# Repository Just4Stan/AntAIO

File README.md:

# AntAIO

Open-source **antweight / beetleweight combat-robot all-in-one** controller — an
ExpressLRS receiver, a 6-axis IMU, and a **triple brushed-DC ESC** on one tiny
board, in the spirit of the [Malenki Nano](https://turnabot.com/products/malenki-nano-integrated-6-channel-triple-electronic-speed-controller-receiver-combo). Built on
the **OpenRX-Lite** ELRS core (ESP32-C3 + SX1281, 2.4 GHz) and forked from
[`incutec-hw/OpenRX`](https://github.com/incutec-hw/OpenRX).

> [!WARNING]
> **Prototype — not validated, not fab-ready.** This board has open
> safety-critical issues (uncommanded drive-motor motion at power-up, and the
> programming interface shares pins with the motor outputs). It drives combat-robot
> motors **including a weapon** — do not build or power it without reading the
> review first. See **[hardware/REVIEW.md](hardware/REVIEW.md)** (full design
> review) and **[CHANGELIST.md](CHANGELIST.md)** (verified to-do list).

## What it is

A single **10.00 × 21.50 mm**, 6-layer board that replaces the usual *RX + 2 drive ESCs +
weapon ESC + gyro* stack of an antweight robot with one MCU-driven combo:

- **Radio link** — ExpressLRS 2.4 GHz (Semtech SX1281) for RC control + telemetry,
  plus the ESP32-C3's own Wi-Fi for OTA config.
- **Motion sensing** — LSM6DS3TR-C 6-axis IMU (gyro + accel) for heading-hold /
  self-right / melty-style control in firmware.
- **Three brushed-DC motor channels** — two drive + one weapon, each a TI DRV8212
  H-bridge fed directly from the battery.
- **Single-cell-friendly power** — buck-boost holds a 5 V rail as the pack sags
  under weapon load, with a linear 3.3 V logic rail and reverse-polarity protection.

Everything is controlled by the **ESP32-C3**: RC decode, mixing, gyro stabilization,
and the three motor PWM outputs all run on-chip.

## Architecture

```
            +BATT (1–2S LiPo)
              │
        Q2  AON7407  ── reverse-polarity P-FET
              ├─────────────► VM ─► DRV8212 ×3 ─► LEFT / RIGHT drive + WEAPON motors
              │
        U8  TPS63070 buck-boost ─► +5V ─► U4 TLV75533 LDO ─► +3V3 (logic)
                                                              │
   ┌──────────────────────────────────────────────────────────┤
   │                                                            │
 U1 ESP32-C3 ──SPI──► U3 SX1281 (2.4 GHz ELRS) ─► FL1 BPF ─► link antenna
   │            └────► U2 LSM6DS3TR-C IMU                 ESP Wi-Fi ─► AE1
   ├── 3× PWM ─► DRV8212 IN/EN  (U6 LEFT, U10 RIGHT, U11 WEAPON)
   ├── ADC ──── VSENSE (battery voltage divider)
   └── GPIO ──► WS2812B status LED (D1)
```

## Specifications

| Block | Part | Notes |
|---|---|---|
| **MCU** | Espressif **ESP32-C3FH4** (U1, QFN-32) | RISC-V, 4 MB embedded flash, 2.4 GHz Wi-Fi |
| **Link radio** | Semtech **SX1281** (U3) | 2.4 GHz, internal DC-DC, 52 MHz TCXO (OSC1), BPF FL1 (2450FM07D0034T) → link antenna |
| **IMU** | **LSM6DS3TR-C** (U2) | 6-axis accel+gyro, 4-wire SPI on the shared radio bus, dedicated CS |
| **Motor drivers** | 3× TI **DRV8212DSGR** | U6 = LEFT drive, U10 = RIGHT drive, U11 = WEAPON; PH/EN mode; VM = +BATT |
| **Buck-boost** | TI **TPS63070** (U8) | +BATT → 5 V; holds the rail across the 1S–2S sag range |
| **LDO** | **TLV75533PDQNR** (U4) | 5 V → 3.3 V logic rail |
| **Reverse protection** | **AON7407** P-FET (Q2) | on +BATT |
| **Status LED** | WS2812B (D1) | addressable RGB |
| **Battery** | **1–2S LiPo (≤ 8.4 V)** | DRV8212 VM is 12 V abs-max — **2S is the hard ceiling; 3S destroys the drivers** |
| **Board** | 10.00 × 21.50 mm, 6-layer | components both sides |

## I/O pads

Solder pads carry the external interface (silk in parentheses):

| Pad | Net | Function |
|---|---|---|
| `+` / `–` | `+BATT` / `GND` | Battery in (1–2S) |
| `5U` | `+5V` | 5 V buck-boost output (servo / accessory) |
| `GND` | `GND` | Ground |
| `S` | GPIO | Signal / spare control pad |
| `BOOT` | GPIO 9 | Hold low at power-up for UART download mode |
| `R` / `T` | UART0 RX / TX | Flashing & serial console (also the right-drive lines — flash with motor battery OFF) |

Motor outputs (OUT1/OUT2 of each DRV8212) and the weapon channel land on the large
copper pads along the board edge.

## ESP32-C3 pin map (as currently drawn)

| GPIO | Pin | Function | GPIO | Pin | Function |
|---|---|---|---|---|---|
| 0 | 4 | VSENSE (battery ADC) | 8 | 14 | WS2812 LED *(strap)* |
| 1 | 5 | Radio DIO1 | 9 | 15 | BOOT *(strap)* |
| 2 | 6 | IMU CS *(strap)* | 10 | 16 | WEAPON_EN |
| 3 | 8 | Radio BUSY | 18 | 25 | LEFT_PH *(USB D−)* |
| 4 | 9 | SPI MOSI | 19 | 26 | LEFT_EN *(USB D+)* |
| 5 | 10 | SPI MISO | U0RXD | 27 | RIGHT_PH |
| 6 | 12 | SPI SCK | U0TXD | 28 | RIGHT_EN |
| 7 | 13 | Radio NSS | GND/EP | 33 | GND |

> [!IMPORTANT]
> The drive-motor enables currently sit on the USB (GPIO18/19) and UART0
> (U0RXD/U0TXD) pins, which are driven **high at reset** — enabling both drive
> motors before firmware runs. The planned fix re-maps PH↔EN onto reset-quiet pins
> and gates the H-bridges behind a default-off arm switch. **Do not treat this pin
> map as final** — track it in [CHANGELIST.md](CHANGELIST.md).

## Flashing

- **UART:** hold `BOOT` low, power-cycle, flash over the `R`/`T` (U0RXD/U0TXD) pads
  **with the motor battery disconnected** (these pins also drive the right motor).
- **Wi-Fi OTA:** ExpressLRS SoftAP, after an initial wired flash.

The ELRS link runs upstream **ExpressLRS** (`Unified_ESP32C3_2400_RX`, ≥ 3.5.0).
The combat-robot mixing, IMU stabilization, and motor-PWM control are application
firmware layered on top (separate; not in this hardware repo).

## Repository

AntAIO began as a fork of [`incutec-hw/OpenRX`](https://github.com/incutec-hw/OpenRX)
— the **OpenRX-Lite** ELRS core (ESP32-C3 + SX1281) extended into a combat-robot
all-in-one. The other OpenRX receiver variants are not part of this repo.

```
AntAIO/
├── hardware/             AntAIO board: ELRS RX + IMU + triple brushed ESC
│   ├── AntAIO.kicad_{pro,sch,pcb}
│   ├── esp32c3_sx1281_lite.kicad_sch   ELRS core sub-sheet
│   ├── REVIEW.md         full design review (pin/datasheet/electrical)
│   └── DESIGN.md
├── shared/libs/          project-local KiCad symbols / footprints / 3D models
├── shared/elrs-targets/  ExpressLRS hardware-target JSON
├── datasheets/common/    local datasheet cache
├── images/               board renders
└── CHANGELIST.md         verified open / done items
```

KiCad 9/10; **project-local libraries only** (no global dependencies). Board renders
are produced with the shared `render_board.py` tool (vias + solder paste stripped,
transparent square).

## License

Hardware: **CERN Open Hardware Licence Version 2 — Strongly Reciprocal**
([CERN-OHL-S-2.0](https://ohwr.org/cern_ohl_s_v2.txt)). See [LICENSE](LICENSE).
Firmware: MIT.

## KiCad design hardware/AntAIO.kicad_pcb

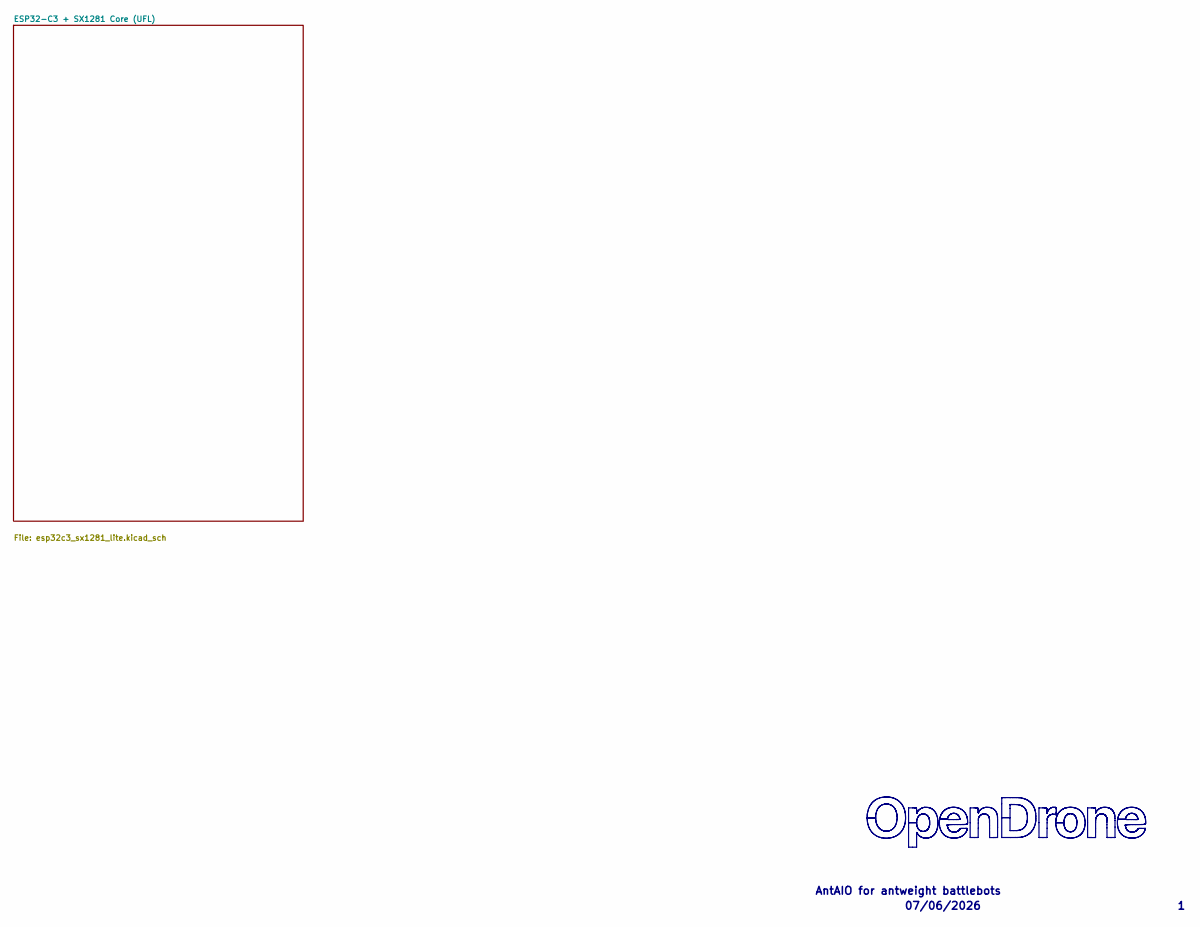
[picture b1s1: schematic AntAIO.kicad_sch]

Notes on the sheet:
07/06/2026
AntAIO for antweight battlebots

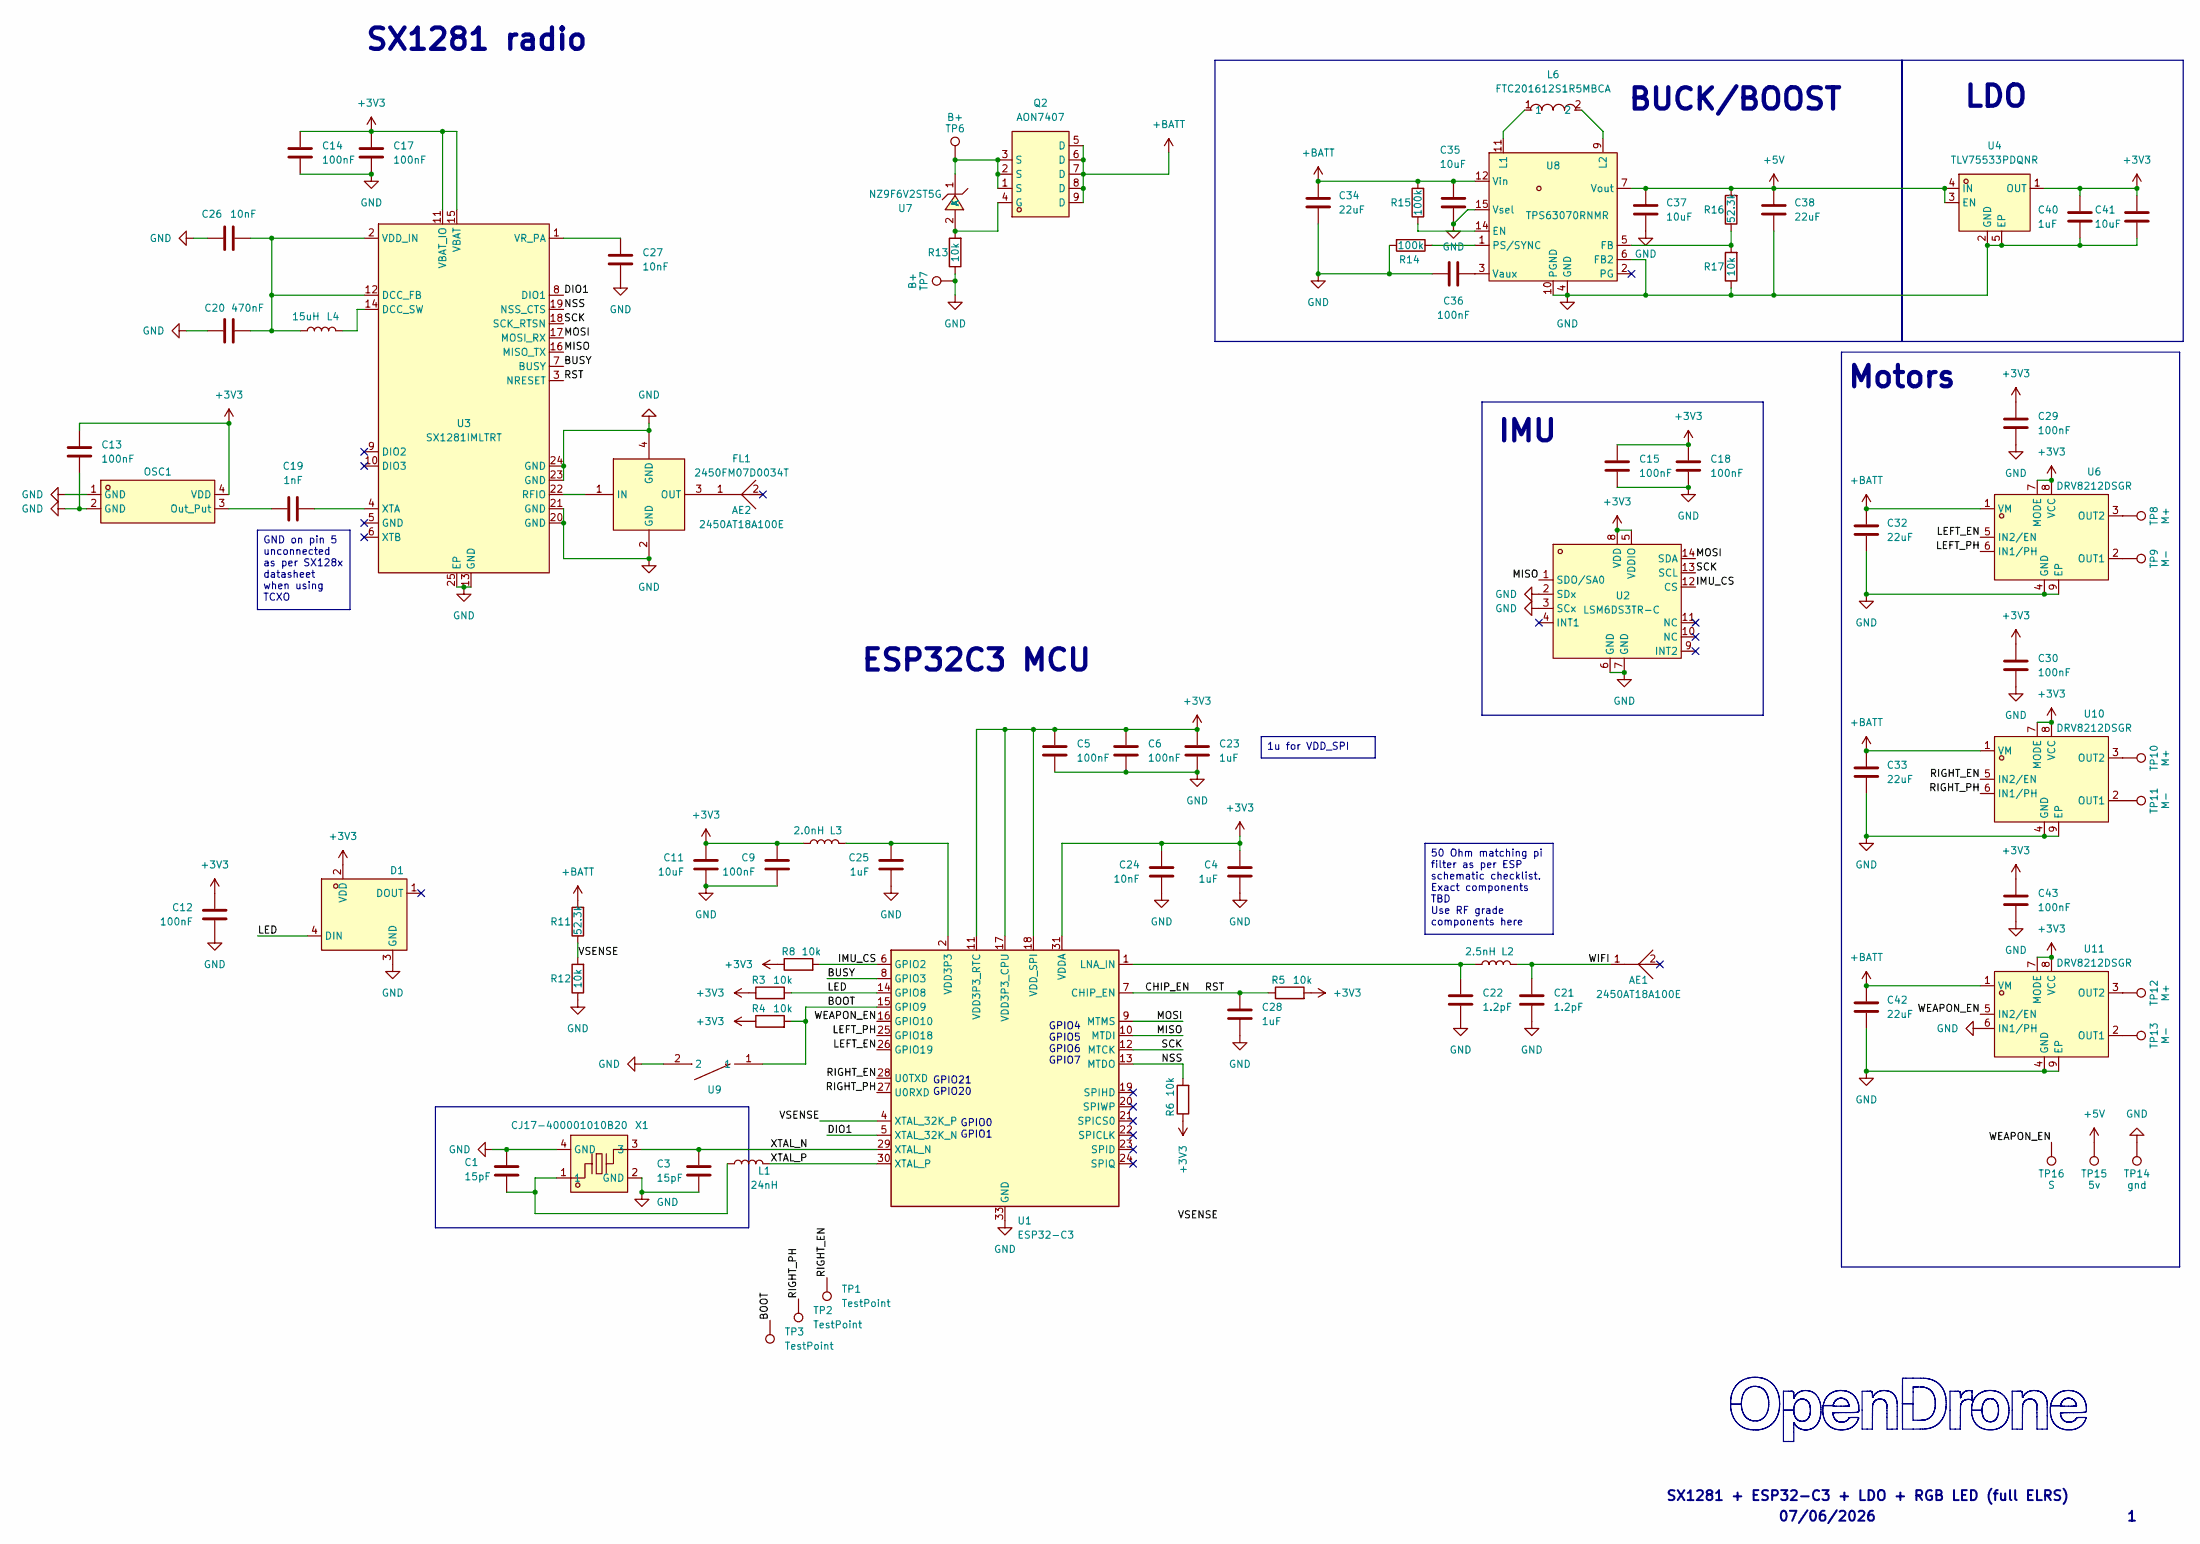
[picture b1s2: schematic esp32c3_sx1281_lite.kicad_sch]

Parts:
AE1, AE2: 2450AT18A100E; ANT-SMD_L3.2-W1.6; LCSC Part C89334
C1, C3: 15pF; C_0201_0603Metric; LCSC C85891
C4, C23, C25, C28, C40: 1uF; C_0201_0603Metric; LCSC C76935
C5, C6, C9, C12, C13, C14, C15, C17, C18, C29, C30, C36, C43: 100nF; C_0201_0603Metric; LCSC C76939
C11: 10uF; C_0402_1005Metric; LCSC C76991
C19: 1nF; C_0201_0603Metric; LCSC C66942
C20: 470nF; C_0201_0603Metric; LCSC C85926
C21, C22: 1.2pF; C_0201_0603Metric; LCSC C85895
C24, C26, C27: 10nF; C_0201_0603Metric; LCSC C2168164
C32, C33, C34, C38, C42: 22uF; C_0805_2012Metric; LCSC C45783
C35, C37: 10uF; C_0603_1608Metric; LCSC C92487
C41: 10uF; C_0402_1005Metric; LCSC C15525
D1: XL-1010RGBC-WS2812B; LED-SMD_4P-L1.0-W1.0-TL_XL-1010RGBC-WS2812B; LCSC Part C5349953
FL1: 2450FM07D0034T; FILTER-SMD_4P-L1.0-W0.5-L; MPN 2450FM07D0034T; LCSC Part C2651081
L1: 24nH; L_0201_0603Metric; LCSC C206441
L2: 2.5nH; L_0201_0603Metric; LCSC C206435
L3: 2.0nH; L_0201_0603Metric; LCSC C86125
L4: 15uH; L_0805_2012Metric
L6: FTC201612S1R5MBCA; IND-SMD_L2.0-W1.6; MPN FTC201612S1R5MBCA; LCSC Part C5832350
OSC1: OW7EL89CENUNFAYLC-52M; OSC-SMD_4P-L2.0-W1.6-BL_TXC_7Z; LCSC Part C22434896
Q2: AON7407; DFN-8_L3.0-W3.0-P0.65-BL; MPN AON7407; LCSC Part C176756
R3, R4, R5, R6, R8, R12, R13, R17: 10k; R_0201_0603Metric; LCSC C106225
R11, R16: 52.3k; R_0201_0603Metric; LCSC C2575555
R14, R15: 100k; R_0201_0603Metric; LCSC C106224
TP1, TP2, TP3: TestPoint; TestPoint_Pad_D1.0mm
TP6, TP7: B+; SolderPad_1.2x2.0mm
TP8, TP10, TP12: M+; SolderPad_1.2x2.0mm
TP9, TP11, TP13: M-; SolderPad_1.2x2.0mm
TP14: gnd; SolderPad_1.2x2.0mm
TP15: 5v; SolderPad_1.2x2.0mm
TP16: S; SolderPad_1.2x2.0mm
U1: ESP32-C3; QFN-32-1EP_5x5mm_P0.5mm_EP3.7x3.7mm
U2: LSM6DS3TR-C; LGA-14_3x2.5mm_P0.5mm_LayoutBorder3x4y; MPN LSM6DS3TR-C; LCSC Part C967633
U3: SX1281IMLTRT; QFN-24_L4.0-W4.0-P0.50-TL-EP2.6; LCSC Part C2151551
U4: TLV75533PDQNR; X2SON-4_L1.0-W1.0-P0.65-TL-EP; LCSC Part C2861882
U6, U10, U11: DRV8212DSGR; WSON-8_L2.0-W2.0-P0.50-TL-EP; MPN DRV8212DSGR; LCSC Part C2843766
U7: NZ9F6V2ST5G; SOD-923_L0.8-W0.6-LS1.0-RD; MPN NZ9F6V2ST5G; LCSC Part C896533
U8: TPS63070RNMR; VQFN-15_L3.0-W2.5-P0.50-BL; MPN TPS63070RNMR; LCSC Part C109322
U9: TS2306A 240GF MSM 9_C2976675; SW-SMD_4P-L3.0-W2.0-P0.85-LS3.5; LCSC Part C2976675
X1: CJ17-400001010B20; CRYSTAL-SMD_4P-L1.6-W1.2-BL; LCSC Part C2875272

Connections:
+3V3: C4.1, C5.1, C6.1, C9.1, C11.1, C12.1, C13.1, C14.1, C15.1, C17.1, C18.1, C23.1, C24.1, C29.1, C30.1, C40.1, C41.1, C43.1, D1.2 (VDD), L3.2, OSC1.4 (VDD), R3.1, R4.1, R5.2, R6.1, R8.1, U1.11 (VDD3P3_RTC), U1.17 (VDD3P3_CPU), U1.18 (VDD_SPI), U1.31 (VDDA), U1.32 (VDDA), U2.5 (VDDIO), U2.8 (VDD), U3.11 (VBAT_IO), U3.15 (VBAT), U4.1 (OUT), U6.7 (MODE), U6.8 (VCC), U10.7 (MODE), U10.8 (VCC), U11.7 (MODE), U11.8 (VCC)
+5V: C37.1, C38.1, R16.2, TP15.1 (1_1), U4.3 (EN), U4.4 (IN), U8.7 (Vout)
+BATT: C32.1, C33.1, C34.1, C35.1, C42.1, Q2.5 (D), Q2.6 (D), Q2.7 (D), Q2.8 (D), Q2.9 (D), R11.2, R15.2, U6.1 (VM), U8.12 (Vin), U10.1 (VM), U11.1 (VM)
/ESP32-C3 + SX1281 Core (UFL)/BOOT: R4.2, TP3.1 (1_1), U1.15 (GPIO9), U9.1
/ESP32-C3 + SX1281 Core (UFL)/BUSY: U1.8 (GPIO3), U3.7 (BUSY)
/ESP32-C3 + SX1281 Core (UFL)/CHIP_EN: C28.1, R5.1, U1.7 (CHIP_EN), U3.3 (NRESET)
/ESP32-C3 + SX1281 Core (UFL)/DIO1: U1.5 (XTAL_32K_N), U3.8 (DIO1)
/ESP32-C3 + SX1281 Core (UFL)/IMU_CS: R8.2, U1.6 (GPIO2), U2.12 (CS)
/ESP32-C3 + SX1281 Core (UFL)/LED: D1.4 (DIN), R3.2, U1.14 (GPIO8)
/ESP32-C3 + SX1281 Core (UFL)/LEFT_EN: U1.26 (GPIO19), U6.5 (IN2/EN)
/ESP32-C3 + SX1281 Core (UFL)/LEFT_PH: U1.25 (GPIO18), U6.6 (IN1/PH)
/ESP32-C3 + SX1281 Core (UFL)/MISO: U1.10 (MTDI), U2.1 (SDO/SA0), U3.16 (MISO_TX)
/ESP32-C3 + SX1281 Core (UFL)/MOSI: U1.9 (MTMS), U2.14 (SDA), U3.17 (MOSI_RX)
/ESP32-C3 + SX1281 Core (UFL)/NSS: R6.2, U1.13 (MTDO), U3.19 (NSS_CTS)
/ESP32-C3 + SX1281 Core (UFL)/RIGHT_EN: TP1.1 (1_1), U1.28 (U0TXD), U10.5 (IN2/EN)
/ESP32-C3 + SX1281 Core (UFL)/RIGHT_PH: TP2.1 (1_1), U1.27 (U0RXD), U10.6 (IN1/PH)
/ESP32-C3 + SX1281 Core (UFL)/SCK: U1.12 (MTCK), U2.13 (SCL), U3.18 (SCK_RTSN)
/ESP32-C3 + SX1281 Core (UFL)/VSENSE: R11.1, R12.2, U1.4 (XTAL_32K_P)
/ESP32-C3 + SX1281 Core (UFL)/WEAPON_EN: TP16.1 (1_1), U1.16 (GPIO10), U11.5 (IN2/EN)
/ESP32-C3 + SX1281 Core (UFL)/WIFI: AE1.1, C21.1, L2.1
/ESP32-C3 + SX1281 Core (UFL)/XTAL_N: C3.1, U1.29 (XTAL_N), X1.3
/ESP32-C3 + SX1281 Core (UFL)/XTAL_P: L1.2, U1.30 (XTAL_P)
GND: C1.2, C3.2, C4.2, C5.2, C6.2, C9.2, C11.2, C12.2, C13.2, C14.2, C15.2, C17.2, C18.2, C20.1, C21.2, C22.2, C23.2, C24.2, C25.2, C26.1, C27.2, C28.2, C29.2, C30.2, C32.2, C33.2, C34.2, C35.2, C36.1, C37.2, C38.2, C40.2, C41.2, C42.2, C43.2, D1.3 (GND), FL1.2 (GND), FL1.4 (GND), OSC1.1 (GND), OSC1.2 (GND), R12.1, R13.1, R14.2, R17.1, TP7.1 (1_1), TP14.1 (1_1), U1.33 (GND), U2.2 (SDx), U2.3 (SCx), U2.6 (GND), U2.7 (GND), U3.13 (GND), U3.20 (GND), U3.21 (GND), U3.23 (GND), U3.24 (GND), U3.25 (EP), U4.2 (GND), U4.5 (EP), U6.4 (GND), U6.9 (EP), U8.4 (GND), U8.6 (FB2), U8.10 (PGND), U8.15 (Vsel), U9.2, U10.4 (GND), U10.9 (EP), U11.4 (GND), U11.6 (IN1/PH), U11.9 (EP), X1.2 (GND), X1.4 (GND)
unnamed: C1.1, L1.1, X1.1
unnamed: C25.1, L3.1, U1.2 (VDD3P3), U1.3 (VDD3P3)
unnamed: FL1.1 (IN), U3.22 (RFIO)
unnamed: AE2.1, FL1.3 (OUT)
unnamed: C19.1, OSC1.3 (Out_Put)
unnamed: Q2.4 (G), R13.2, U7.2 (A)
unnamed: C22.1, L2.2, U1.1 (LNA_IN)
unnamed: C20.2, C26.2, L4.1, U3.2 (VDD_IN), U3.12 (DCC_FB)
unnamed: L4.2, U3.14 (DCC_SW)
unnamed: C27.1, U3.1 (VR_PA)
unnamed: C19.2, U3.4 (XTA)
unnamed: TP9.1 (1_1), U6.2 (OUT1)
unnamed: TP8.1 (1_1), U6.3 (OUT2)
unnamed: Q2.1 (S), Q2.2 (S), Q2.3 (S), TP6.1 (1_1), U7.1 (K)
unnamed: R15.1, U8.14 (EN)
unnamed: R16.1, R17.2, U8.5 (FB)
unnamed: L6.1, U8.11 (L1)
unnamed: L6.2, U8.9 (L2)
unnamed: R14.1, U8.1 (PS/SYNC)
unnamed: C36.2, U8.3 (Vaux)
unnamed: TP11.1 (1_1), U10.2 (OUT1)
unnamed: TP10.1 (1_1), U10.3 (OUT2)
unnamed: TP13.1 (1_1), U11.2 (OUT1)
unnamed: TP12.1 (1_1), U11.3 (OUT2)

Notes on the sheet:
GPIO0 GPIO1
SX1281 + ESP32-C3 + LDO + RGB LED (full ELRS)
GPIO21 GPIO20
Motors
LDO
BUCK/BOOST
IMU
GPIO4 GPIO5 GPIO6 GPIO7
SX1281 radio
ESP32C3 MCU
07/06/2026
GND on pin 5 unconnected as per SX128x datasheet when using TCXO
1u for VDD_SPI
50 Ohm matching pi filter as per ESP schematic checklist. Exact components TBD Use RF grade components here

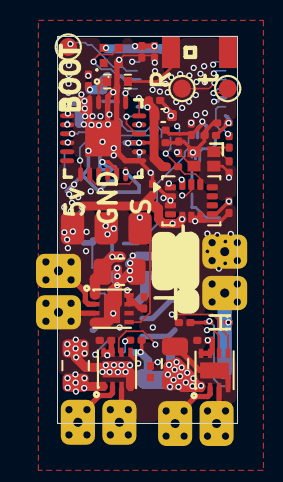
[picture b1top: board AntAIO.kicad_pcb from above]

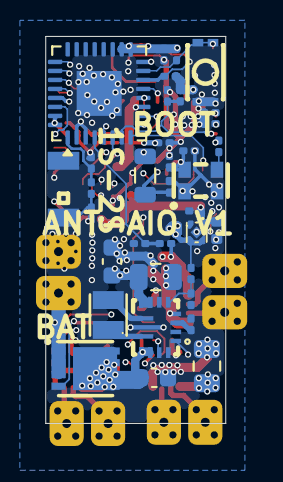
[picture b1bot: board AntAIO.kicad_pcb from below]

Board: 6 copper layers, 10.0 x 21.5 mm, 84 parts (35 on the bottom side), 47 nets.

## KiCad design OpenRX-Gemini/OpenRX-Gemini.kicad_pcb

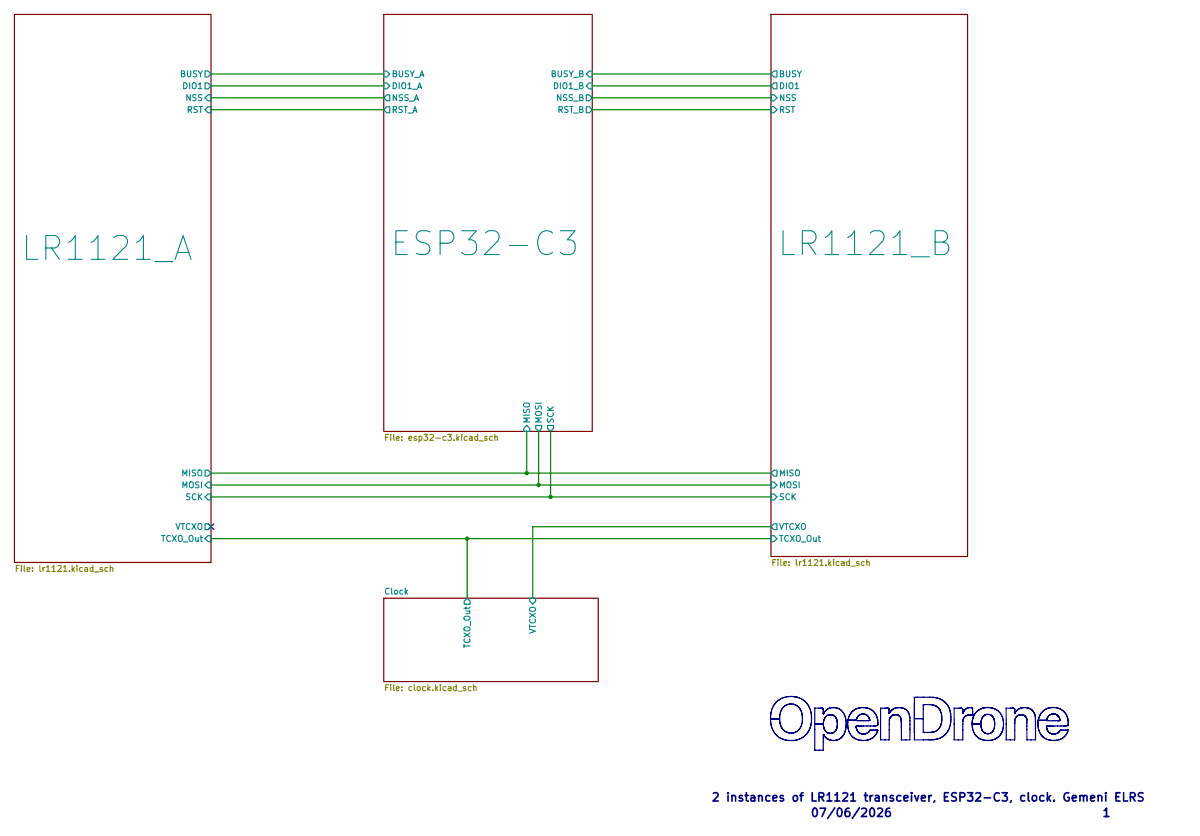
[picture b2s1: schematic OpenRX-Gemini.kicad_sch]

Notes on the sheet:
07/06/2026
2 instances of LR1121 transceiver, ESP32-C3, clock. Gemeni ELRS

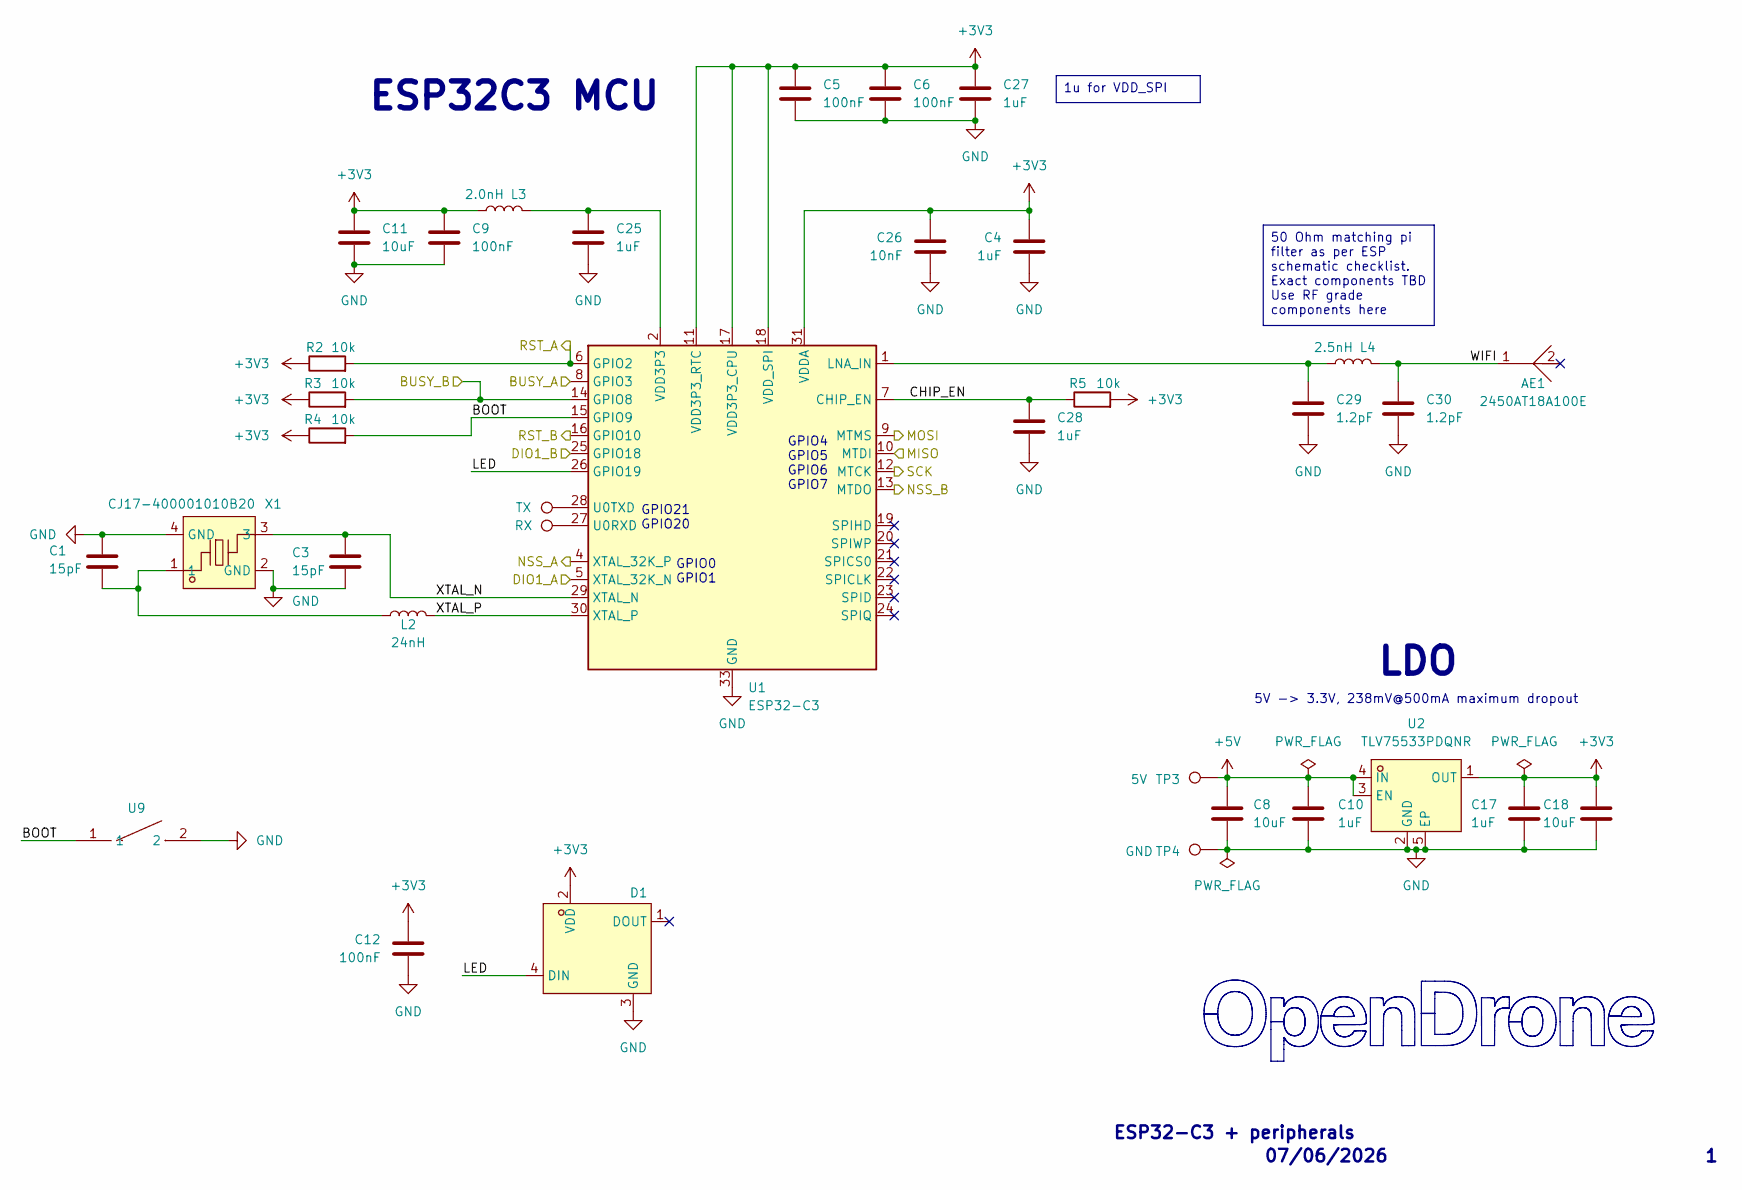
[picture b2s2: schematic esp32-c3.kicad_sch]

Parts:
AE1: 2450AT18A100E; ANT-SMD_L3.2-W1.6; LCSC Part C89334
C1, C3: 15pF; C_0201_0603Metric; LCSC C85891
C4, C10, C17, C25, C27, C28: 1uF; C_0201_0603Metric; LCSC C76935
C5, C6, C9, C12: 100nF; C_0201_0603Metric; LCSC C76939
C8, C18: 10uF; C_0402_1005Metric; LCSC C15525
C11: 10uF; C_0402_1005Metric; LCSC C76991
C26: 10nF; C_0201_0603Metric; LCSC C2168164
C29, C30: 1.2pF; C_0201_0603Metric; LCSC C85895
D1: XL-1010RGBC-WS2812B; LED-SMD_4P-L1.0-W1.0-TL_XL-1010RGBC-WS2812B; LCSC Part C5349953
L2: 24nH; L_0201_0603Metric; LCSC C206441
L3: 2.0nH; L_0201_0603Metric; LCSC C86125
L4: 2.5nH; L_0201_0603Metric; LCSC C206435
R2, R3, R4, R5: 10k; R_0201_0603Metric; LCSC C106225
TP1: RX; SolderPad_1.2x2.0mm
TP2: TX; SolderPad_1.2x2.0mm
TP3: 5V; SolderPad_1.2x2.0mm
TP4: GND; SolderPad_1.2x2.0mm
U1: ESP32-C3; QFN-32-1EP_5x5mm_P0.5mm_EP3.7x3.7mm
U2: TLV75533PDQNR; X2SON-4_L1.0-W1.0-P0.65-TL-EP; LCSC Part C2861882
U9: TS2306A 240GF MSM 9_C2976675; SW-SMD_4P-L3.0-W2.0-P0.85-LS3.5; LCSC Part C2976675
X1: CJ17-400001010B20; CRYSTAL-SMD_4P-L1.6-W1.2-BL; LCSC Part C2875272

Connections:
+3V3: C4.1, C5.1, C6.1, C9.1, C11.1, C12.1, C17.1, C18.1, C26.1, C27.1, D1.2 (VDD), L3.2, R2.1, R3.1, R4.1, R5.2, U1.11 (VDD3P3_RTC), U1.17 (VDD3P3_CPU), U1.18 (VDD_SPI), U1.31 (VDDA), U1.32 (VDDA), U2.1 (OUT); also elsewhere on the board
+5V: C8.1, C10.1, TP3.1 (1_1), U2.3 (EN), U2.4 (IN)
/ESP32-C3/BOOT: R4.2, U1.15 (GPIO9), U9.1
/ESP32-C3/BUSY_A: U1.8 (GPIO3); also elsewhere on the board
/ESP32-C3/BUSY_B: R3.2, U1.14 (GPIO8); also elsewhere on the board
/ESP32-C3/CHIP_EN: C28.1, R5.1, U1.7 (CHIP_EN)
/ESP32-C3/DIO1_A: U1.5 (XTAL_32K_N); also elsewhere on the board
/ESP32-C3/DIO1_B: U1.25 (GPIO18); also elsewhere on the board
/ESP32-C3/LED: D1.4 (DIN), U1.26 (GPIO19)
/ESP32-C3/MISO: U1.10 (MTDI); also elsewhere on the board
/ESP32-C3/MOSI: U1.9 (MTMS); also elsewhere on the board
/ESP32-C3/NSS_A: U1.4 (XTAL_32K_P); also elsewhere on the board
/ESP32-C3/NSS_B: U1.13 (MTDO); also elsewhere on the board
/ESP32-C3/RST_A: R2.2, U1.6 (GPIO2); also elsewhere on the board
/ESP32-C3/RST_B: U1.16 (GPIO10); also elsewhere on the board
/ESP32-C3/SCK: U1.12 (MTCK); also elsewhere on the board
/ESP32-C3/WIFI: AE1.1, C30.1, L4.1
/ESP32-C3/XTAL_N: C3.1, U1.29 (XTAL_N), X1.3
/ESP32-C3/XTAL_P: L2.2, U1.30 (XTAL_P)
GND: C1.2, C3.2, C4.2, C5.2, C6.2, C8.2, C9.2, C10.2, C11.2, C12.2, C17.2, C18.2, C25.2, C26.2, C27.2, C28.2, C29.2, C30.2, D1.3 (GND), TP4.1 (1_1), U1.33 (GND), U2.2 (GND), U2.5 (EP), U9.2, X1.2 (GND), X1.4 (GND); also elsewhere on the board
unnamed: C1.1, L2.1, X1.1
unnamed: C25.1, L3.1, U1.2 (VDD3P3), U1.3 (VDD3P3)
unnamed: C29.1, L4.2, U1.1 (LNA_IN)
unnamed: TP1.1 (1_1), U1.27 (U0RXD)
unnamed: TP2.1 (1_1), U1.28 (U0TXD)

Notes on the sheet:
ESP32C3 MCU
07/06/2026
GPIO21 GPIO20
GPIO0 GPIO1
5V -> 3.3V, 238mV@500mA maximum dropout
GPIO4 GPIO5 GPIO6 GPIO7
LDO
ESP32-C3 + peripherals
50 Ohm matching pi filter as per ESP schematic checklist. Exact components TBD Use RF grade components here
1u for VDD_SPI

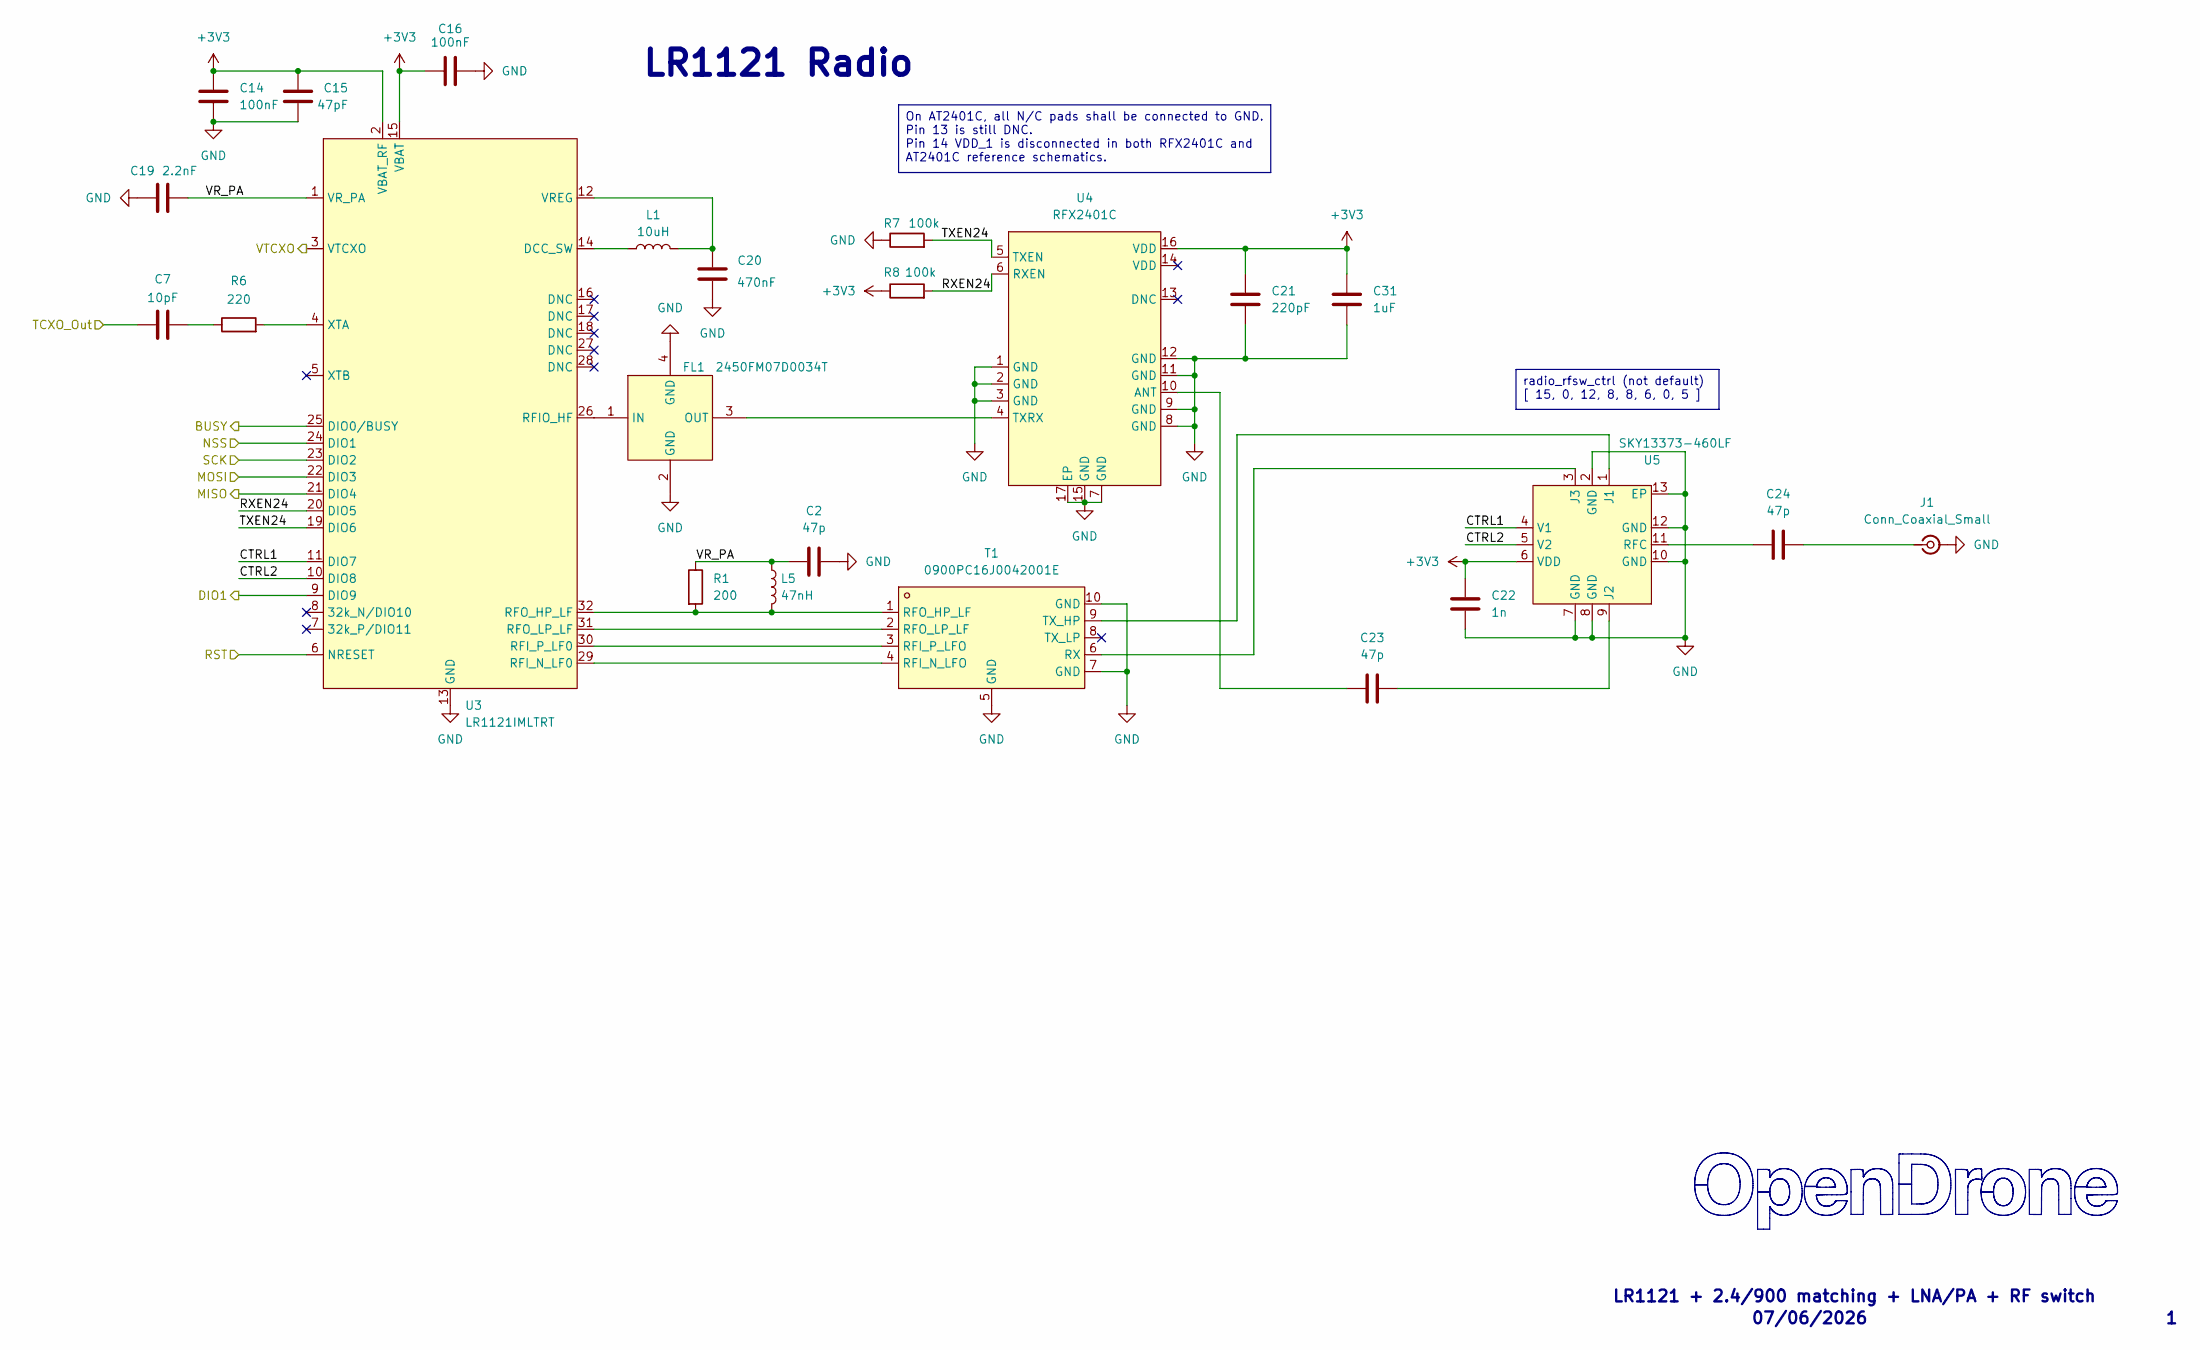
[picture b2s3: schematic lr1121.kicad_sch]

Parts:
C2, C23, C24: 47p; C_0201_0603Metric; LCSC C85908
C7: 10pF; C_0201_0603Metric; LCSC C384956
C14, C16: 100nF; C_0201_0603Metric; LCSC C76939
C15: 47pF; C_0201_0603Metric; LCSC C85908
C19: 2.2nF; C_0201_0603Metric; LCSC C161488
C20: 470nF; C_0201_0603Metric; LCSC C85926
C21: 220pF; C_0201_0603Metric; LCSC C907939
C22: 1n; C_0201_0603Metric; LCSC C85934
C31: 1uF; C_0201_0603Metric; LCSC C76935
FL1: 2450FM07D0034T; FILTER-SMD_4P-L1.0-W0.5-L; MPN 2450FM07D0034T; LCSC Part C2651081
J1: Conn_Coaxial_Small; U.FL_Hirose_U.FL-R-SMT-1_Vertical; LCSC C88374
L1: 10uH; L_0603_1608Metric; LCSC C194437
L5: 47nH; L_0402_1005Metric; LCSC C192855
R1: 200; R_0201_0603Metric; LCSC C274337
R6: 220; R_0201_0603Metric; LCSC C2074788
R7, R8: 100k; R_0201_0603Metric; LCSC C106224
T1: 0900PC16J0042001E; FILTER-SMD_10P-L2.0-W1.6-BL; LCSC Part C19842466
U3: LR1121IMLTRT; QFN-32-1EP_5x5mm_P0.5mm_EP3.7x3.7mm; LCSC Part C7498014
U4: RFX2401C; QFN-16_L3.0-W3.0-P0.50-BL-EP1.7; LCSC Part C19213
U5: SKY13373-460LF; QFN-12_EP_2x2_Pitch0.5mm

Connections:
+3V3: C14.1, C15.1, C16.1, C21.1, C22.1, C31.1, R8.1, U3.2 (VBAT_RF), U3.15 (VBAT), U4.16 (VDD), U5.6 (VDD); also elsewhere on the board
/Clock/TCXO_Out: C7.2; also elsewhere on the board
/ESP32-C3/BUSY_A: U3.25 (DIO0/BUSY); also elsewhere on the board
/ESP32-C3/DIO1_A: U3.9 (DIO9); also elsewhere on the board
/ESP32-C3/MISO: U3.21 (DIO4); also elsewhere on the board
/ESP32-C3/MOSI: U3.22 (DIO3); also elsewhere on the board
/ESP32-C3/NSS_A: U3.24 (DIO1); also elsewhere on the board
/ESP32-C3/RST_A: U3.6 (NRESET); also elsewhere on the board
/ESP32-C3/SCK: U3.23 (DIO2); also elsewhere on the board
/LR1121_A/CTRL1: U3.11 (DIO7), U5.4 (V1)
/LR1121_A/CTRL2: U3.10 (DIO8), U5.5 (V2)
/LR1121_A/RXEN24: R8.2, U3.20 (DIO5), U4.6 (RXEN)
/LR1121_A/TXEN24: R7.2, U3.19 (DIO6), U4.5 (TXEN)
/LR1121_A/VR_PA: C2.1, C19.1, L5.1, R1.1, U3.1 (VR_PA)
/LR1121_A/VTCXO: U3.3 (VTCXO)
GND: C2.2, C14.2, C15.2, C16.2, C19.2, C20.1, C21.2, C22.2, C31.2, FL1.2 (GND), FL1.4 (GND), J1.2 (Ext), R7.1, T1.5 (GND), T1.7 (GND), T1.10 (GND), U3.13 (GND), U3.33 (EP), U4.1 (GND), U4.2 (GND), U4.3 (GND), U4.7 (GND), U4.8 (GND), U4.9 (GND), U4.11 (GND), U4.12 (GND), U4.15 (GND), U4.17 (EP), U5.2 (GND), U5.7 (GND), U5.8 (GND), U5.10 (GND), U5.12 (GND), U5.13 (EP); also elsewhere on the board
unnamed: C7.1, R6.1
unnamed: FL1.1 (IN), U3.26 (RFIO_HF)
unnamed: FL1.3 (OUT), U4.4 (TXRX)
unnamed: C24.2, J1.1 (In)
unnamed: T1.4 (RFI_N_LFO), U3.29 (RFI_N_LF0)
unnamed: T1.3 (RFI_P_LFO), U3.30 (RFI_P_LF0)
unnamed: L5.2, R1.2, T1.1 (RFO_HP_LF), U3.32 (RFO_HP_LF)
unnamed: T1.2 (RFO_LP_LF), U3.31 (RFO_LP_LF)
unnamed: T1.6 (RX), U5.3 (J3)
unnamed: T1.9 (TX_HP), U5.1 (J1)
unnamed: L1.1, U3.14 (DCC_SW)
unnamed: C20.2, L1.2, U3.12 (VREG)
unnamed: R6.2, U3.4 (XTA)
unnamed: C23.1, U4.10 (ANT)
unnamed: C23.2, U5.9 (J2)
unnamed: C24.1, U5.11 (RFC)

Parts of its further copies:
C33: 2.2nF; C_0201_0603Metric; LCSC C161488
C34: 10pF; C_0201_0603Metric; LCSC C384956
C35, C37: 100nF; C_0201_0603Metric; LCSC C76939
C36: 47pF; C_0201_0603Metric; LCSC C85908
C38: 470nF; C_0201_0603Metric; LCSC C85926
C39, C42, C44: 47p; C_0201_0603Metric; LCSC C85908
C40: 220pF; C_0201_0603Metric; LCSC C907939
C41: 1uF; C_0201_0603Metric; LCSC C76935
C43: 1n; C_0201_0603Metric; LCSC C85934
FL2: 2450FM07D0034T; FILTER-SMD_4P-L1.0-W0.5-L; MPN 2450FM07D0034T; LCSC Part C2651081
J2: Conn_Coaxial_Small; U.FL_Hirose_U.FL-R-SMT-1_Vertical; LCSC C88374
L6: 10uH; L_0603_1608Metric; LCSC C194437
L7: 47nH; L_0402_1005Metric; LCSC C192855
R9: 220; R_0201_0603Metric; LCSC C2074788
R10: 200; R_0201_0603Metric; LCSC C274337
R11, R12: 100k; R_0201_0603Metric; LCSC C106224
T2: 0900PC16J0042001E; FILTER-SMD_10P-L2.0-W1.6-BL; LCSC Part C19842466
U6: LR1121IMLTRT; QFN-32-1EP_5x5mm_P0.5mm_EP3.7x3.7mm; LCSC Part C7498014
U7: RFX2401C; QFN-16_L3.0-W3.0-P0.50-BL-EP1.7; LCSC Part C19213
U8: SKY13373-460LF; QFN-12_EP_2x2_Pitch0.5mm

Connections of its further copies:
+3V3: C35.1, C36.1, C37.1, C40.1, C41.1, C43.1, R12.1, U6.2 (VBAT_RF), U6.15 (VBAT), U7.16 (VDD), U8.6 (VDD); also elsewhere on the board
/Clock/TCXO_Out: C34.2; also elsewhere on the board
/Clock/VTCXO: U6.3 (VTCXO); also elsewhere on the board
/ESP32-C3/BUSY_B: U6.25 (DIO0/BUSY); also elsewhere on the board
/ESP32-C3/DIO1_B: U6.9 (DIO9); also elsewhere on the board
/ESP32-C3/MISO: U6.21 (DIO4); also elsewhere on the board
/ESP32-C3/MOSI: U6.22 (DIO3); also elsewhere on the board
/ESP32-C3/NSS_B: U6.24 (DIO1); also elsewhere on the board
/ESP32-C3/RST_B: U6.6 (NRESET); also elsewhere on the board
/ESP32-C3/SCK: U6.23 (DIO2); also elsewhere on the board
/LR1121_B/CTRL1: U6.11 (DIO7), U8.4 (V1)
/LR1121_B/CTRL2: U6.10 (DIO8), U8.5 (V2)
/LR1121_B/RXEN24: R12.2, U6.20 (DIO5), U7.6 (RXEN)
/LR1121_B/TXEN24: R11.2, U6.19 (DIO6), U7.5 (TXEN)
/LR1121_B/VR_PA: C33.1, C39.1, L7.1, R10.1, U6.1 (VR_PA)
GND: C33.2, C35.2, C36.2, C37.2, C38.1, C39.2, C40.2, C41.2, C43.2, FL2.2 (GND), FL2.4 (GND), J2.2 (Ext), R11.1, T2.5 (GND), T2.7 (GND), T2.10 (GND), U6.13 (GND), U6.33 (EP), U7.1 (GND), U7.2 (GND), U7.3 (GND), U7.7 (GND), U7.8 (GND), U7.9 (GND), U7.11 (GND), U7.12 (GND), U7.15 (GND), U7.17 (EP), U8.2 (GND), U8.7 (GND), U8.8 (GND), U8.10 (GND), U8.12 (GND), U8.13 (EP); also elsewhere on the board
unnamed: C34.1, R9.1
unnamed: FL2.1 (IN), U6.26 (RFIO_HF)
unnamed: FL2.3 (OUT), U7.4 (TXRX)
unnamed: C44.2, J2.1 (In)
unnamed: T2.4 (RFI_N_LFO), U6.29 (RFI_N_LF0)
unnamed: T2.3 (RFI_P_LFO), U6.30 (RFI_P_LF0)
unnamed: L7.2, R10.2, T2.1 (RFO_HP_LF), U6.32 (RFO_HP_LF)
unnamed: T2.2 (RFO_LP_LF), U6.31 (RFO_LP_LF)
unnamed: T2.6 (RX), U8.3 (J3)
unnamed: T2.9 (TX_HP), U8.1 (J1)
unnamed: L6.1, U6.14 (DCC_SW)
unnamed: C38.2, L6.2, U6.12 (VREG)
unnamed: R9.2, U6.4 (XTA)
unnamed: C42.1, U7.10 (ANT)
unnamed: C42.2, U8.9 (J2)
unnamed: C44.1, U8.11 (RFC)

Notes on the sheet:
LR1121 + 2.4/900 matching + LNA/PA + RF switch
LR1121 Radio
07/06/2026
radio_rfsw_ctrl (not default) [ 15, 0, 12, 8, 8, 6, 0, 5 ]
On AT2401C, all N/C pads shall be connected to GND. Pin 13 is still DNC. Pin 14 VDD_1 is disconnected in both RFX2401C and AT2401C reference schematics.
